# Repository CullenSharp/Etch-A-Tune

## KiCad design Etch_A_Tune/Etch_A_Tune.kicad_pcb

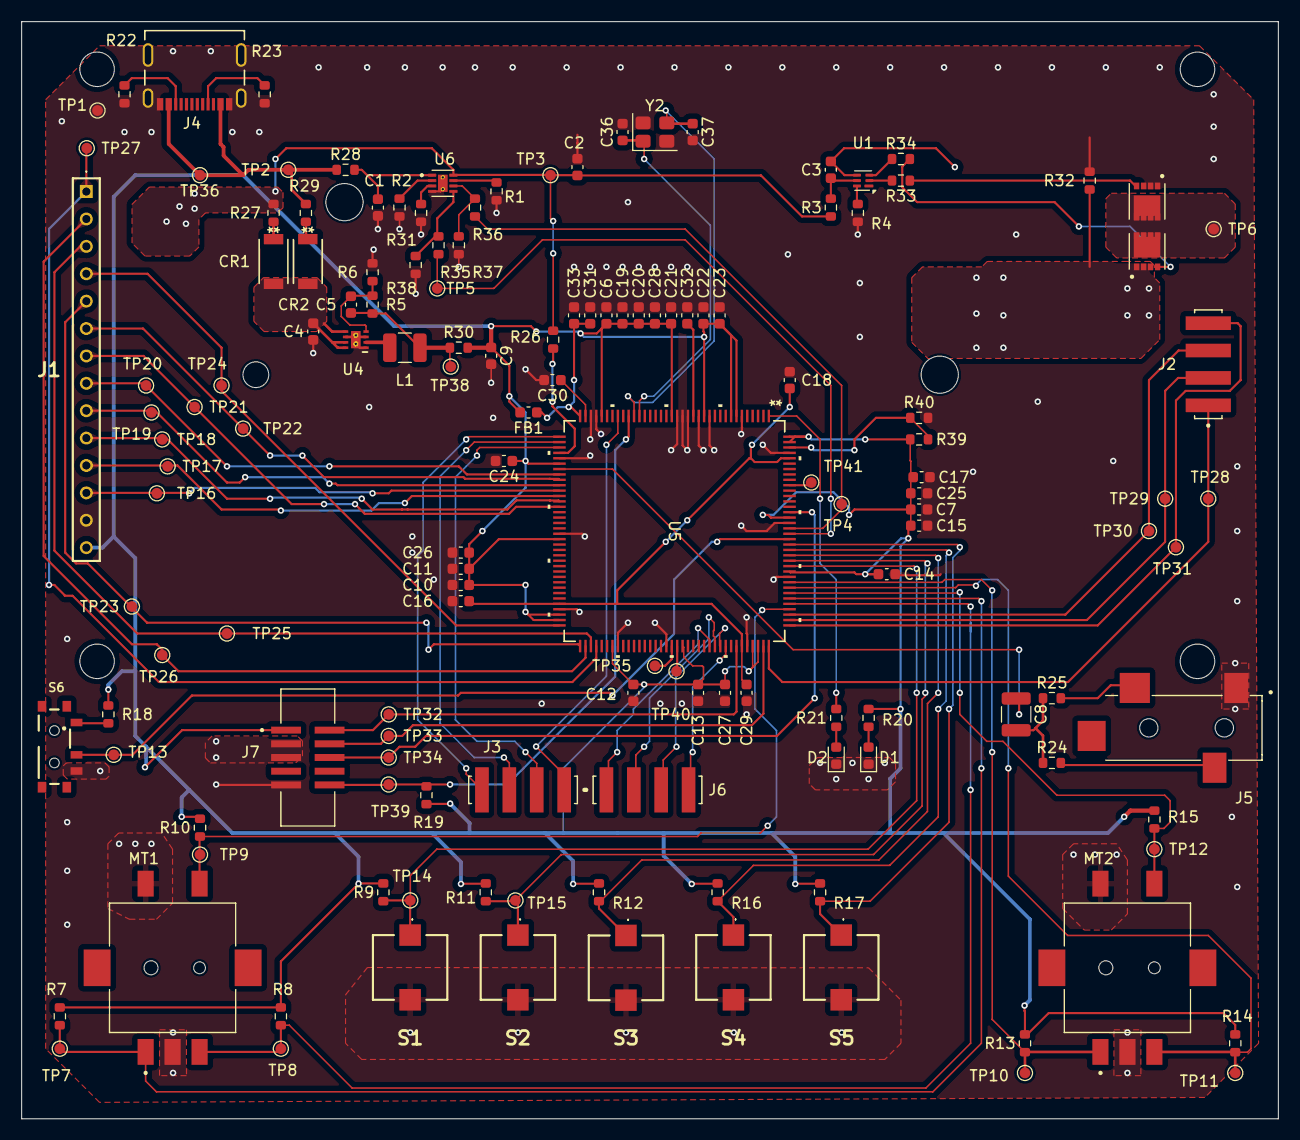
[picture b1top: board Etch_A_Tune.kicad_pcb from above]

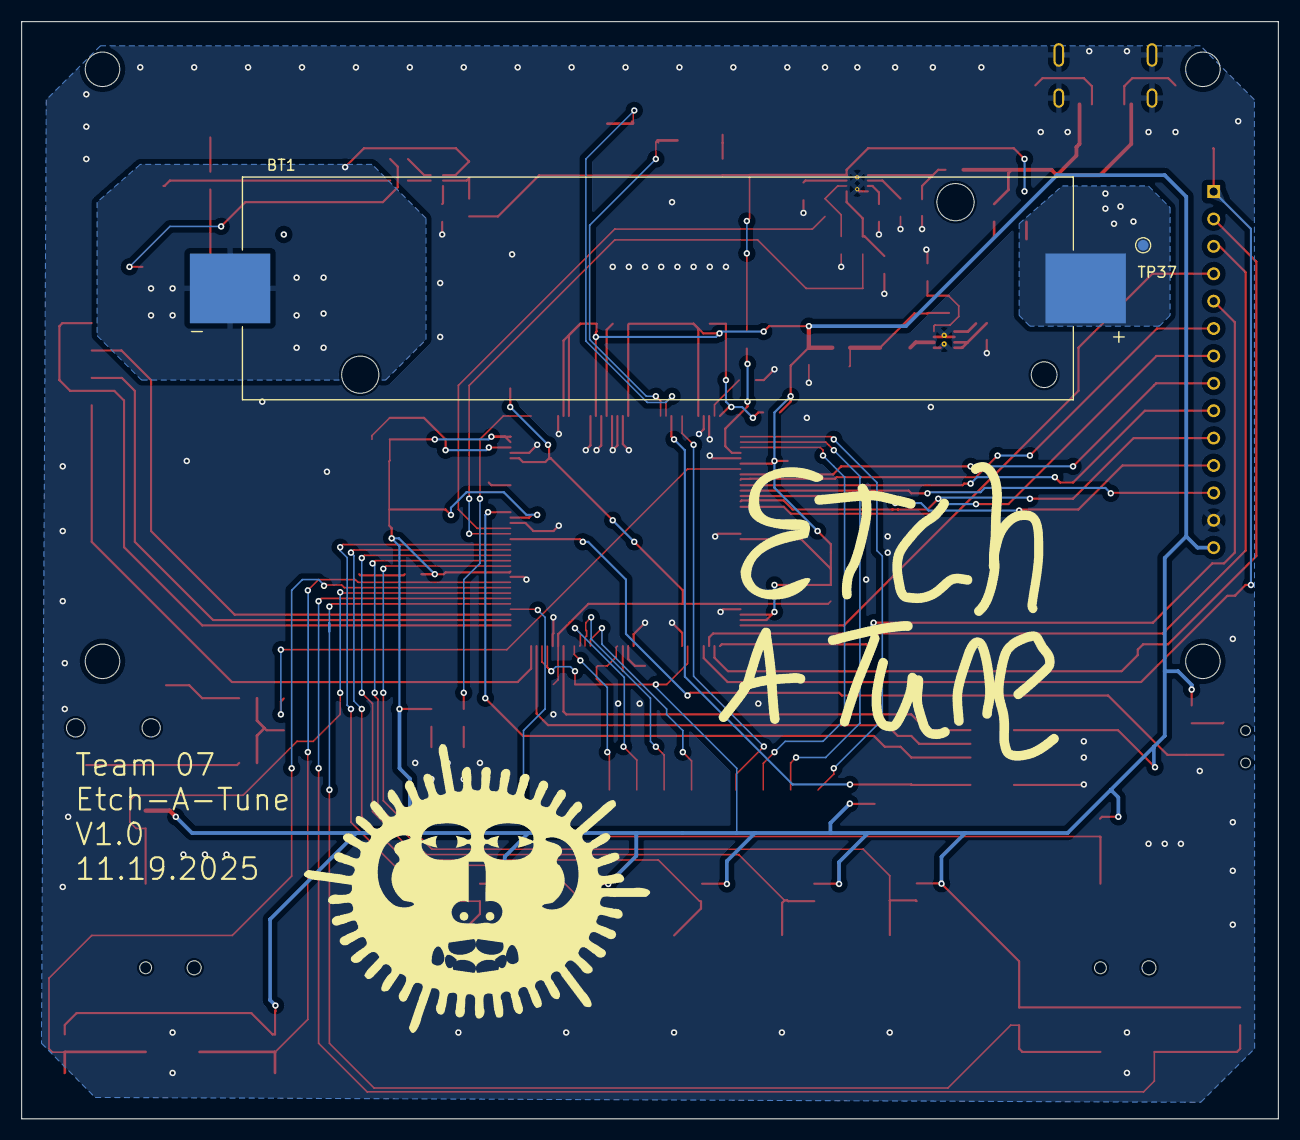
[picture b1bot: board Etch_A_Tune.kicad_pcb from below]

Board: 2 copper layers, 116.5 x 101.7 mm, 145 parts (2 on the bottom side), 87 nets.

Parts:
BT1: 1042P; BAT_1042P
C1, C2, C12, C25, C30, C31: 1uF; C_0603_1608Metric
C3: .1uF; C_0603_1608Metric
C4, C9: 10uF; C_0603_1608Metric
C5: 22pF; C_0603_1608Metric
C6, C7, C10, C11, C13, C14, C15, C16, C17, C18, C19, C20, C21, C22, C23, C24, C26, C28, C29: 100nF; C_0603_1608Metric
C8: 330uF; C_1210_3225Metric
C27: 4.7uF; C_0603_1608Metric
C32: 220pF; C_0603_1608Metric
C33: 1nF; C_0603_1608Metric
C36, C37: 18pf; C_0603_1608Metric
CR1, CR2: CMS06TE12L_Q_M; M-FLAT_TOS-L
D1, D2: 150060GS75000; LED_0603_1608Metric
FB1: FerriteBead_Small; C_0603_1608Metric
J1: 75915-414LF; 75915414LF
J2, J3, J6: 91601-304ALF; AMPHENOL_91601-304ALF
J4: 2171790001; MOLEX_2171790001
J5: SJ-3524-SMT-PI; CUI_SJ-3524-SMT-PI
J7: 3220-10-0300-00; CNC_3220-10-0300-00
L1: 1UH; L_1210_3225Metric
MT1, MT2: RIC11-31S15D7-GSMT; XDCR_RIC11-31S15D7-GSMT
R1: 27k; R_0603_1608Metric
R2: 604; R_0603_1608Metric
R3: 330; R_0603_1608Metric
R4: 2.2k; R_0603_1608Metric
R5: 360k; R_0603_1608Metric
R6: 180k; R_0603_1608Metric
R7, R8, R9, R10, R11, R12, R13, R14, R15, R16, R17, R18, R19, R31: 10k; R_0603_1608Metric
R20, R21: 10; R_0603_1608Metric
R22, R23: 5.1k; R_0603_1608Metric
R24, R25, R26, R27, R28, R29, R30, R32, R33, R34, R35, R36, R37, R38, R39, R40: 0; R_0603_1608Metric
S1, S2, S3, S4, S5: B3AL-1005P; B3AL1005P
S6: 450404015514
TP1, TP2, TP3, TP4, TP5, TP6, TP7, TP8, TP9, TP10, TP11, TP12, TP13, TP14, TP15, TP16, TP17, TP18, TP19, TP20, TP21, TP22, TP23, TP24, TP25, TP26, TP27, TP28, TP29, TP30, TP31, TP32, TP33, TP34, TP36, TP37, TP38, TP39: TestPoint; TestPoint_Pad_D1.0mm
TP35: USB5V; TestPoint_Pad_D1.0mm
TP40: USB3V3; TestPoint_Pad_D1.0mm
TP41: BOOT0; TestPoint_Pad_D1.0mm
U1: BQ297xy; WSON-6_1.5x1.5mm_P0.5mm
U2, U3: CSD16406Q3; TRANS_CSD16406Q3
U4: TPS62063DSGR; DSG0008A
U5: STM32H7A3ZIT6Q; LQFP-144-L
U6: BQ25170DSGR; SON50P200X200X80-9N
Y2: 12Mhz; Crystal_SMD_Abracon_ABM8G-4Pin_3.2x2.5mm

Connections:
+3.3V: C6.1, C7.1, C9.1, C10.1, C11.1, C12.1, C13.1, C14.1, C15.1, C17.1, C19.1, C20.1, C21.1, C22.1, C23.1, C24.1, C25.1, C26.1, C27.1, C28.1, FB1.2, J1.14, J7.1, R7.1, R8.1, R9.1, R10.1, R11.1, R12.1, R13.1, R14.1, R15.1, R16.1, R17.1, R18.1, R19.1, R20.1, R30.2, R39.2, U5.7 (VDD), U5.8 (VBAT), U5.13 (VDD), U5.19 (VDD), U5.32 (VDD), U5.42 (VDD), U5.56 (VDD), U5.70 (VDDLDO), U5.71 (VDD), U5.79 (VDD), U5.92 (VDD), U5.105 (VDDLDO), U5.106 (VDD), U5.119 (VDDMMC), U5.129 (VDD), U5.143 (VDDLDO), U5.144 (VDD)
/Battery/BAT_DIAG: R35.2, TP5.1, U5.126 (PG13)
/Battery/BAT_V_SENSE: R26.1, U5.40 (PA3)
/Battery/CHARGE_GATE: R33.2, U1.2 (Cout)
/Battery/DISCHARGE_GATE: R34.1, U1.3 (Dout)
/Battery/PACK+: BT1.P, C2.1, R3.1, R26.2, R27.1, TP3.1, TP37.1, U6.8 (OUT)
/Battery/PG: R36.2, TP4.1, U5.127 (PG14)
/Battery/USB_Charge: J4.A4B9 (VBUS1), J4.B4A9 (VBUS2), R28.1, R29.1, TP2.1, TP36.1
/CS: J1.12, TP16.1, U5.47 (PC4)
/Controllers/ROTA1: MT1.A, R7.2, TP7.1, U5.114 (PD2)
/Controllers/ROTA2: MT2.A, R13.2, TP10.1, U5.117 (PD5)
/Controllers/ROTB1: MT1.B, R8.2, TP8.1, U5.113 (PD1)
/Controllers/ROTB2: MT2.B, R14.2, TP11.1, U5.116 (PD4)
/Controllers/ROTP1: MT1.E, R10.2, TP9.1, U5.112 (PD0)
/Controllers/ROTP2: MT2.E, R15.2, TP12.1, U5.115 (PD3)
/Controllers/SW1: R9.2, S1.1, TP14.1, U5.120 (PD6)
/Controllers/SW2: R11.2, S2.1, TP15.1, U5.121 (PD7)
/Controllers/SW3: R12.2, S3.1, U5.122 (PG9)
/Controllers/SW4: R16.2, S4.1, U5.123 (PG10)
/Controllers/SW5: R17.2, S5.1, U5.124 (PG11)
/Controllers/SlideSwitch: S6.2, TP13.1, U5.125 (PG12)
/DC/RS: J1.10, TP18.1, U5.49 (PB0)
/LED: J1.7, TP21.1, U5.50 (PB1)
/Microcontroller/DAC_OUT: C8.1, U5.43 (PA4)
/PA0: J3.04, U5.37 (PA0)
/PA1: J3.03, U5.38 (PA1)
/PA2: J3.02, U5.39 (PA2)
/PA8: J6.01, U5.97 (PA8)
/PA9: J6.02, U5.98 (PA9)
/PA10: J6.03, U5.99 (PA10)
/PA11: J6.04, U5.100 (PA11)
/PC1: J3.01, U5.29 (PC1)
/RESET: J1.11, TP17.1, U5.48 (PC5)
/SCK: J1.8, TP20.1, U5.44 (PA5)
/SDI (MOSI): J1.9, TP19.1, U5.46 (PA7)
/SDO(MISO): J1.6, TP22.1, U5.45 (PA6)
/SD_CS: J2.01, TP28.1, U5.108 (PA15)
/SD_MISO: J2.03, TP30.1, U5.111 (PC12)
/SD_MOSI: J2.02, TP29.1, U5.110 (PC11)
/SD_SCK: J2.04, TP31.1, U5.109 (PC10)
/SWCLK: J7.4, TP33.1, U5.107 (PA14)
/SWDIO: J7.2, TP32.1, U5.102 (PA13)
/SWO: J7.6, TP34.1, U5.130 (PB3)
/T_CLK: J1.5, TP23.1, U5.73 (PB13)
/T_CS: J1.4, TP24.1, U5.72 (PB12)
/T_DIN: J1.3, TP25.1, U5.75 (PB15)
/T_DO: J1.2, TP26.1, U5.74 (PB14)
/T_IRQ: J1.1, TP27.1, U5.76 (PD8)
/nRESET: J7.10, R19.2, TP39.1, U5.27 (NRST)
GND: C1.2, C2.2, C4.2, C6.2, C7.2, C9.2, C10.2, C11.2, C12.2, C13.2, C14.2, C15.2, C16.1, C17.2, C18.1, C19.2, C20.2, C21.2, C22.2, C23.2, C24.2, C25.2, C26.2, C27.2, C28.2, C29.1, C30.2, C31.2, C32.2, C33.2, C36.2, C37.2, D1.1 (K), D2.1 (K), J1.13, J4.A1B12 (GND1), J4.B1A12 (GND2), J4.SH1 (SHIELD1), J4.SH2 (SHIELD2), J4.SH3 (SHIELD3), J4.SH4 (SHIELD4), J5.1, J7.3, J7.5, J7.9, MT1.C, MT1.D, MT2.C, MT2.D, R1.2, R2.2, R4.2, R6.2, R22.2, R23.2, R31.2, R32.2, R37.1, R38.1, R40.2, S1.2, S2.2, S3.2, S4.2, S5.2, S6.3, TP1.1, U3.1, U3.2, U3.3, U4.1 (PGND), U4.3 (AGND), U4.6 (MODE), U4.9 (PAD), U4.GND, U5.6 (VSS), U5.12 (VSS), U5.14 (VSSSMPS), U5.16 (VDDSMPS), U5.17 (VFBSMPS), U5.18 (VSS), U5.33 (VSS), U5.34 (VSSA), U5.41 (VSS), U5.55 (VSS), U5.69 (VSS), U5.80 (VSS), U5.89 (VSS), U5.104 (VSS), U5.118 (VSS), U5.128 (VSS), U5.141 (VSS), U6.4 (GND), U6.9 (EXP), U6.10, U6.11, Y2.2, Y2.4
unnamed: C5.1, L1.2, R5.1, R30.1, TP38.1
unnamed: C8.2, R24.1, R25.1
unnamed: CR1.1, R27.2
unnamed: CR2.1, R29.2
unnamed: D1.2 (A), R20.2
unnamed: D2.2 (A), R21.2
unnamed: J4.A5 (CC1), R23.1
unnamed: J4.B5 (CC2), R22.1
unnamed: J5.2, R25.2
unnamed: J5.3, R24.2
unnamed: R18.2, S6.1
unnamed: R33.1, U3.4
unnamed: R34.2, U2.4
unnamed: TP6.1, U2.5, U2.6, U2.7, U2.8, U3.5, U3.6, U3.7, U3.8
unnamed: C3.1, R3.2, U1.5 (BAT)
unnamed: R4.1, U1.6 (V-)
unnamed: BT1.N, C3.2, R32.1, U1.4 (VSS), U2.1, U2.2, U2.3
unnamed: C4.1, CR1.2, CR2.2, U4.5 (EN), U4.7 (AVIN), U4.8 (PVIN)
unnamed: C5.2, R5.2, R6.1, U4.4 (FB)
unnamed: L1.1, U4.2 (SW)
unnamed: R21.1, U5.1 (PE2)
unnamed: C31.1, C33.1, FB1.1, U5.36 (VDDA)
unnamed: C32.1, U5.15 (VLXSMPS)
unnamed: C30.1, U5.35 (VREF+)
unnamed: TP41.1, U5.135 (BOOT0)
unnamed: R39.1, R40.1, U5.142 (PDR_ON)
unnamed: TP40.1, U5.91 (VDD33USB)
unnamed: TP35.1, U5.90 (VDD50USB)
unnamed: C1.1, R28.2, U6.1 (IN)
unnamed: R2.1, U6.2 (ISET)
unnamed: R35.1, R38.2, U6.5 (STAT)
unnamed: R31.1, U6.3 (TS)
unnamed: R1.1, U6.7 (VSET)
unnamed: R36.1, R37.2, U6.6 (~PG)
OSC_H_IN: C36.1, U5.25 (PH0-OSC_IN), Y2.1
OSC_H_OUT: C37.1, U5.26 (PH1-OSC_OUT), Y2.3
VCORE: C16.2, C18.2, C29.2, U5.68 (VCAP), U5.103 (VCAP), U5.140 (VCAP)

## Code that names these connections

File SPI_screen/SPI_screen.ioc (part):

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Mcu.Name=STM32H7A3Z(G-I)TxQ
Mcu.Package=LQFP144
Mcu.UserName=STM32H7A3ZITxQ
PA0.GPIOParameters=GPIO_Speed,GPIO_Label
PA0.GPIO_Label=XP
PA0.GPIO_Speed=GPIO_SPEED_FREQ_VERY_HIGH
PA0.Signal=GPIO_Output
PA1.GPIOParameters=GPIO_Label,GPIO_Pd
PA1.GPIO_Label=YP
PA1.GPIO_Pd=GPIO_PULLDOWN
PA1.Signal=SharedAnalog_PA1
PA13.Mode=Serial_Wire
PA13.Signal=DEBUG_JTMS-SWDIO
PA14.Mode=Serial_Wire
PA14.Signal=DEBUG_JTCK-SWCLK
PA2.GPIOParameters=GPIO_Label,GPIO_Pd
PA2.GPIO_Label=XM
PA2.GPIO_Pd=GPIO_PULLDOWN
PA2.Signal=ADCx_INP14
PA3.GPIOParameters=GPIO_Label
PA3.GPIO_Label=BAT_V_SENSE
PA3.Mode=IN15-Single-Ended
PA3.Signal=ADC1_INP15
PA4.GPIOParameters=GPIO_Label
PA4.GPIO_Label=AUDIO_OUT
PA4.Signal=COMP_DAC11_group
PA5.GPIOParameters=GPIO_Speed,PinState,GPIO_Label
PA5.GPIO_Label=LCD_RD
PA5.GPIO_Speed=GPIO_SPEED_FREQ_VERY_HIGH
PA5.PinState=GPIO_PIN_SET
PA5.Signal=GPIO_Output
PA6.GPIOParameters=GPIO_Speed,GPIO_Label
PA6.GPIO_Label=LCD_D0
PA6.GPIO_Speed=GPIO_SPEED_FREQ_VERY_HIGH
PA6.Signal=GPIO_Output
PA7.GPIOParameters=GPIO_Speed,PinState,GPIO_Label
PA7.GPIO_Label=LCD_WR
PA7.GPIO_Speed=GPIO_SPEED_FREQ_VERY_HIGH
PA7.PinState=GPIO_PIN_SET
PA7.Signal=GPIO_Output
PA8.GPIOParameters=GPIO_Speed,GPIO_Label
PA8.GPIO_Label=LCD_D6
PA8.GPIO_Speed=GPIO_SPEED_FREQ_VERY_HIGH
PA8.Signal=GPIO_Output
PA9.GPIOParameters=GPIO_Speed,GPIO_Label
PA9.GPIO_Label=LCD_D7
PA9.GPIO_Speed=GPIO_SPEED_FREQ_VERY_HIGH
PA9.Signal=GPIO_Output
PB0.GPIOParameters=GPIO_Speed,GPIO_Label
PB0.GPIO_Label=LCD_RS
PB0.GPIO_Speed=GPIO_SPEED_FREQ_VERY_HIGH
PB0.Signal=GPIO_Output
PB1.GPIOParameters=PinState,GPIO_Label
PB1.GPIO_Label=LCD_BL
PB1.PinState=GPIO_PIN_SET
PB1.Signal=GPIO_Output
PB12.GPIOParameters=GPIO_Speed,GPIO_Label
PB12.GPIO_Label=LCD_D2
PB12.GPIO_Speed=GPIO_SPEED_FREQ_VERY_HIGH
PB12.Signal=GPIO_Output
PB13.GPIOParameters=GPIO_Speed,GPIO_Label
PB13.GPIO_Label=LCD_D1
PB13.GPIO_Speed=GPIO_SPEED_FREQ_VERY_HIGH
PB13.Signal=GPIO_Output
PB14.GPIOParameters=GPIO_Speed,GPIO_Label
PB14.GPIO_Label=LCD_D4
PB14.GPIO_Speed=GPIO_SPEED_FREQ_VERY_HIGH
PB14.Signal=GPIO_Output
PB15.GPIOParameters=GPIO_Speed,GPIO_Label
PB15.GPIO_Label=LCD_D3
PB15.GPIO_Speed=GPIO_SPEED_FREQ_VERY_HIGH
PB15.Signal=GPIO_Output
PC1.GPIOParameters=GPIO_Speed,PinState,GPIO_Label
PC1.GPIO_Label=YM
PC1.GPIO_Speed=GPIO_SPEED_FREQ_VERY_HIGH
PC1.PinState=GPIO_PIN_RESET
PC1.Signal=GPIO_Output
PC14-OSC32_IN.GPIOParameters=GPIO_Label
PC14-OSC32_IN.GPIO_Label=OSC32_IN
PC14-OSC32_IN.Signal=RCC_OSC32_IN
PC15-OSC32_OUT.GPIOParameters=GPIO_Label
PC15-OSC32_OUT.GPIO_Label=OSC32_OUT
PC15-OSC32_OUT.Signal=RCC_OSC32_OUT
PC4.GPIOParameters=GPIO_Speed,PinState,GPIO_Label,GPIO_ModeDefaultOutputPP
PC4.GPIO_Label=LCD_CS
PC4.GPIO_ModeDefaultOutputPP=GPIO_MODE_OUTPUT_PP
PC4.GPIO_Speed=GPIO_SPEED_FREQ_VERY_HIGH
PC4.PinState=GPIO_PIN_SET
PC4.Signal=GPIO_Output
PC5.GPIOParameters=PinState,GPIO_Label
PC5.GPIO_Label=LCD_RST
PC5.PinState=GPIO_PIN_SET
PC5.Signal=GPIO_Output
PD0.GPIOParameters=GPIO_Label
PD0.GPIO_Label=ROTP1
PD0.Signal=GPIO_Input
PD1.GPIOParameters=GPIO_PuPd,GPIO_Label,GPIO_ModeDefaultEXTI
PD1.GPIO_Label=ROTA1
PD1.GPIO_ModeDefaultEXTI=GPIO_MODE_IT_RISING_FALLING
PD1.GPIO_PuPd=GPIO_NOPULL
PD1.Signal=GPXTI1
PD2.GPIOParameters=GPIO_PuPd,GPIO_Label,GPIO_ModeDefaultEXTI
PD2.GPIO_Label=ROTB1
PD2.GPIO_ModeDefaultEXTI=GPIO_MODE_IT_RISING_FALLING
PD2.GPIO_PuPd=GPIO_NOPULL
PD2.Signal=GPXTI2
PD3.GPIOParameters=GPIO_Label
PD3.GPIO_Label=ROTP2
PD3.Signal=GPIO_Input
PD4.GPIOParameters=GPIO_Label
PD4.GPIO_Label=ROTB2
PD4.Signal=GPIO_Input
PD5.GPIOParameters=GPIO_Label
PD5.GPIO_Label=ROTA2
PD5.Signal=GPIO_Input
PD6.GPIOParameters=GPIO_Label
PD6.GPIO_Label=SW1
PD6.Signal=GPIO_Input
PD7.GPIOParameters=GPIO_Label
PD7.GPIO_Label=SW2
PD7.Signal=GPIO_Input
PD8.GPIOParameters=GPIO_Speed,GPIO_Label
PD8.GPIO_Label=LCD_D5
PD8.GPIO_Speed=GPIO_SPEED_FREQ_VERY_HIGH
PD8.Signal=GPIO_Output
PD9.Signal=USART3_RX
PE2.GPIOParameters=GPIO_Label
PE2.GPIO_Label=LED
PE2.Signal=GPIO_Output
PE4.GPIOParameters=GPIO_Speed,PinState,GPIO_Label
PE4.GPIO_Label=TS_CS
PE4.GPIO_Speed=GPIO_SPEED_FREQ_VERY_HIGH
PE4.PinState=GPIO_PIN_SET
PE4.Signal=GPIO_Output
PG10.GPIOParameters=GPIO_Label
PG10.GPIO_Label=SW3
PG10.Signal=GPIO_Input
PG11.GPIOParameters=GPIO_Label
PG11.GPIO_Label=SW5
PG11.Signal=GPIO_Input
PG12.GPIOParameters=GPIO_Label,GPIO_ModeDefaultEXTI
PG12.GPIO_Label=SLIDE_SW
PG12.GPIO_ModeDefaultEXTI=GPIO_MODE_IT_RISING
PG12.Signal=GPXTI12
PG13.GPIOParameters=GPIO_Label
PG13.GPIO_Label=BAT_DIAG
PG13.Signal=GPIO_Input
PG14.GPIOParameters=GPIO_Label
PG14.GPIO_Label=POWER_GOOD
PG14.Signal=GPIO_Input
PG9.GPIOParameters=GPIO_Label
PG9.GPIO_Label=SW3
PG9.Signal=GPIO_Input
PH0-OSC_IN.GPIOParameters=GPIO_Label
PH0-OSC_IN.GPIO_Label=PH0-MCU
PH0-OSC_IN.Signal=RCC_OSC_IN
PH1-OSC_OUT.GPIOParameters=GPIO_Label
PH1-OSC_OUT.GPIO_Label=PH1-MCU
PH1-OSC_OUT.Signal=RCC_OSC_OUT
RCC.HSE_VALUE=8000000
RCC.SYSCLKFreq_VALUE=280000000
RCC.SYSCLKSource=RCC_SYSCLKSOURCE_PLLCLK
board=NUCLEO-H7A3ZI-Q
boardIOC=true

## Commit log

2025-10-23 Etch-a-Tune Product Design Specification
2025-10-26 Adds H7A3_NUCLEO configuration
2025-10-26 Adds README and moves PDS
2025-10-26 Adds contributing information
2025-10-26 Converts contributing page to Markdown
2025-10-28 Added first assignment for docs folder
    Our week 3 assignment of finalizing our project ideas and why we chose what we did
2025-10-28 ECE 411 Team 7 Project Ideas Assignment
    Adding the first assignment we submitted to our docs folder
2025-10-28 Remove duplicated file
2025-10-29 Adds ST7796 driver as a submodule.
2025-10-29 Moved submodule to components directory
2025-10-30 This hell scape
    meeting adjourned
2025-11-02 Removes unused submodules
2025-11-02 Moves st7796 component driver into to main project
2025-11-02 Adds XPT2046 driver as a submodule
2025-11-02 Updates submodules
2025-11-02 Configures spi and updates include paths
2025-11-02 Changes url due to renaming remote repository stm32_st7796
2025-11-02 Adds lcd and ts classes to the board support package
2025-11-03 Corrects typos in .gitmodules and moves .gitignore
2025-11-03 Updated submodules so it actually works
2025-11-03 Removed wrongly named submodule folders
2025-11-03 Hopefully actually fixed submodules
2025-11-03 Adds placeholders for bus configuration
2025-11-03 I think the test data is done. Needs review
2025-11-03 Changes variables to use stm32h7 instead of g0
2025-11-03 Fixed the test data so it should be properly formatted now
2025-11-03 Seperated signal and image into seperate files that should be able to be called from the command line
2025-11-05 Attempt to implement example code from an LCD HAL Display library. It is receiving data, based on the faint image. But it is not correct
2025-11-06 Changed Example to LCD Speed test and updated pin defines
2025-11-06 Updated schematic and preliminary PCB doc
    did rough PCB layout
2025-11-06 The Bread board prototype
    The current progress of the board as of 11-5-2025
2025-11-06 Gannt Chart Deliverable
    Gantt Chart created using GanttProject for the Week 6 Homework assignment - Project Schedule
2025-11-07 Gets screen working
2025-11-07 Working LCD Demo
    The great and powerful Cullen Sharp rewrote the drive initialization to work with the st7796s that our display uses. To be rewritten further
2025-11-07 Updated Bread Board Prototype
    The prototype works and can run example code. Example code is located on the mcma branch and is unmerged as of date.
2025-11-08 Changes names to reflect ST7796 usage
2025-11-08 Touch Screen Calibrated, Connected, and Controlling
    The Demo is set for paint, if new hardware is used, calibration is probably needed/
2025-11-08 Updated VIdeo Demo For paintApp
2025-11-08 Removes erroneous register defines.
2025-11-08 Fixes #15 and #16.
2025-11-10 Adds 320x480 test image simplifies test sequence.
2025-11-10 Moves st7796 function prototypes into st7796.h
2025-11-10 Move register defines to st7796.h
2025-11-10 Rewrite ST7796_SETWINDOW and ST7796_SETCURSOR macroes as functions.
2025-11-11 Converts st7796 macroes to static inline functions.
2025-11-11 Removes functions from adafruit_lcd.c
2025-11-11 Fixes accidental use of 8-bit color.
2025-11-11 Changed App type to Cullen Speed Test
    Files needed to be moved and one changed
2025-11-11 Updated Clocks and Changed orientation
    Current BitmapTest is 69ms
2025-11-12 Configures SPI4 for touch control
2025-11-12 Allocates frame buffers
2025-11-12 Fixes reversed images on draw RGBImage
2025-11-13 Functional Decomposition
    Added the functional decomposition deliverable document to the docs folder. Also slightly updated the gantt chart
2025-11-13 Adds demo code for DAC with TIM6 and DMA
2025-11-13 Schematic Update
    Fixed component Footprints and added new switches/rotary encoders. Wired and placed bypass capacitors for most devices. Removed 5V boost converter because external DAC is no longer being utilized. Pl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
2025-11-13 Etch A Tune V.02
    Updated more foot prints and components onto bom, specifically SWD debug header and 1x14 pin header for touch and screen module. Added 4pin header for SD card reader.
2025-11-13 Etch A Tune BOM
    Forgot to add bom in last push
2025-11-14 Incorporates the CMSIS DSP library and demo wav
    I added the CMSIS DSP library, which was painless... mostly. I haven't had a lot of luck with audio playback though.
    The output from the DAC sounds like a buzz saw.
    There's now a raw unsigned 8-bit 11025Hz WAV file programmed to flash. This is copied to RAM in main.c. From there,
    the data is pushed to the DAC by the DMA.
    The audio file was created with Audacity and xxd. The relevant command was
    xxd -i guitar.raw guitar.h
2025-11-14 Include CMSIS_DSP as middleware
    Recent versions of CMSIS don't include precompiled versions of the DSP
    library. As such, they need to be manually built and included in the
    project. The library's source code is found under Middlewares/CMSIS_DSP
    and included with "arm_math.h".
2025-11-15 Started Enclosure Modeling
    Rough draft without all measurements of the front panel and the knobs.
    Will likely need to scale the knobs down, and re-dimension tolerances once I can measure the parts we have
2025-11-16 Updated parallel power supply
    Updated USB and battery operation and added DAC output
2025-11-16 Added v.03 schematic pdf
2025-11-17 V.04 Schematic
    added 64 pin header LEDS
2025-11-17 Updated schematic
2025-11-18 Final Layout before routing
2025-11-19 Another Update! :D
2025-11-19 pdf docs
2025-11-19 PCB about 75% done
2025-11-19 Update again
2025-11-19 2 Layer Board
    Changed from 4 to 2 layers
2025-11-19 Design Review in docs
    Added the design review notes deliverable to the docs folder
2025-11-20 Update
    Finished Analog Power Domain
2025-11-20 95% finished PCB
    Only changes needed for completion is ferrite bead footprint and DNP crystal osc.
2025-11-20 Update
    Added headers for ADC Pins and 4 extra GPIOs
2025-11-20 Finished PCB
    Added ferrite bead and crystal oscillator. Added silkscreen text and tidied up component designators.
2025-11-20 Update
    Changed DC blocking cap to 1206 footprint, added SVG silkscreen to back of board and added team name date and version
2025-11-20 Adding GBR files
    adding gbr files for 1.0 build of etch a tune, added schematic pdf files as well
2025-11-20 Added PDF files
    added pdf alternatives for PCB
2025-11-22 Updated BOM
    Changed Values for an accurate BOM, and exported results
2025-11-22 Created Interactive BOM
    Make an interactive html bom using KiCAD plugin
2025-11-22 Updated Interactive BOM to exclude DNP
    Reading the Card Explains the Card
2025-11-25 Updates IO configuration
    This brings IO configuration to parity with board design.
2025-11-27 More in depth modeling of enclosure
    Created a PCB and screen parts for assembly and placement visualization
2025-11-27 Making Parts Fit Together
    Spent time making the screen and pcb line up, and fixing the front screen model to match.
    Will need to make a version with a new model of the screen
2025-11-29 Replace XPT2046 driver with simple analog touch driver
2025-11-29 Reconfigure project to use 8bit parallel rgb interface
2025-11-30 Implements pressure sensing
2025-12-02 Shells and Better Fitting
    Still need to account for tolerances that will be needed, but unsure how best to accomplish this.
    Made the shells 1/8 of an inch thick through global variables, so that should make more modeling easier
2025-12-04 Implements pressure sense
    Currently, I'm seeing a bug where the screen coordinates are not correctly mapped to display coordinates. I think this could be solved by implementing a calibration sequence.
2025-12-04 Adds FreeRTOS
2025-12-04 Adds testing plan document
    The testing plan is for the V1.0 hardware and software
2025-12-05 Reconfigure project to use 8bit parallel rgb interface
    I've verified that the wiring, io configuration, and lcd module are
    sound, so I'm leaving this a recovery point.
2025-12-06 Simplifies lcdSpeedTest program
    This is to simplify the integration process with the grts and lcd panel
    driver.
2025-12-06 Incorporate changes to GRTS from cullen_test
    lcd_grts_integration and cullen_test have the same driver for the GRTS
    now.
2025-12-06 Fixes GRTS bugs
    I initially had issues with the ADC sampling while the screen was
    drawing. This was fixed by adding pull downs on the adc inputs, adding
    external rc filters to Xm and Xp pins, increasing the settling time, and
    implementing a stronger digital low-pass filter.
2025-12-07 Implment double buffering with hardware timer
    I setup one of the hardware timers to implement a 30Hz refresh rate. It
    handles this by swapping `write_to` and `draw_from` pointers.
2025-12-07 Implement drawing and displaying tasks
    Using FreeRTOS, I created two tasks `touch_io` and `lcd_display`.
    `touch_io` samples touch input from the resistive touch screen every 20ms and writes it to a
    buffer. `lcd_display` takes the buffer and draws it to the screen.
2025-12-07 Adds placeholder for mode switch interrupt handler
2025-12-07 Adds stub for encoder object
    I still need to implement the IRQ handlers. These should interpret the
    state of the encoder and emit an event to the calling system.
2025-12-08 Adds initial version of encoder driver
    It has one weird bug that turning clockwise decrements the position
    variable. I fixed this by changing the gpio signals associated with
    channel a and channel b.
2025-12-08 Adds pinout data to documentation
    I generated this with CubeMX. Under the pinout tab, select "export
    pinout".
2025-12-08 Adds attribution to Adafruit
2025-12-08 Integrates single interrupt based encoder
2025-12-08 Removes alternate functions from pinout listing
2025-12-11 Made Model Presentable
2025-12-13 Presentation PDF Added
